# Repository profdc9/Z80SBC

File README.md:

# Z80 Single Board Computer

This is a PCB layout by Daniel Marks of Grant Searle's 9 chip CP/M computer as obtained from

http://searle.x10host.com/cpm/index.html

You need to follow his instructions on how to flash the memory and install CP/M.

http://searle.x10host.com/cpm/z80sbcFiles.zip

This design uses a 28C256 (32k X 8 EEPROM) rather than the original 27128 (16 x 8 EPROM).  JP6 needs to be set to the 16K setting, and only the first 16K of the EEPROM needs to be programmed.

I have added a 8255A peripheral interface and a SPI serial peripheral interface port.  I plan on modifying the SD card driver to use the faster hardware on this board, using the SD card loader here:

http://xepb.org/dtz/sgsbcsd.html

The SPI peripheral will hopefully allow other hardware to be easily added such as an ethernet interface (Wiznet or enc28j60) for TCP/IP, a SPI LCD for display, etc.  JP2 selects the clockspeed of the SPI, either 1/2 of 7.3278 MHz (slow clock) or 16 MHz (fast clock).

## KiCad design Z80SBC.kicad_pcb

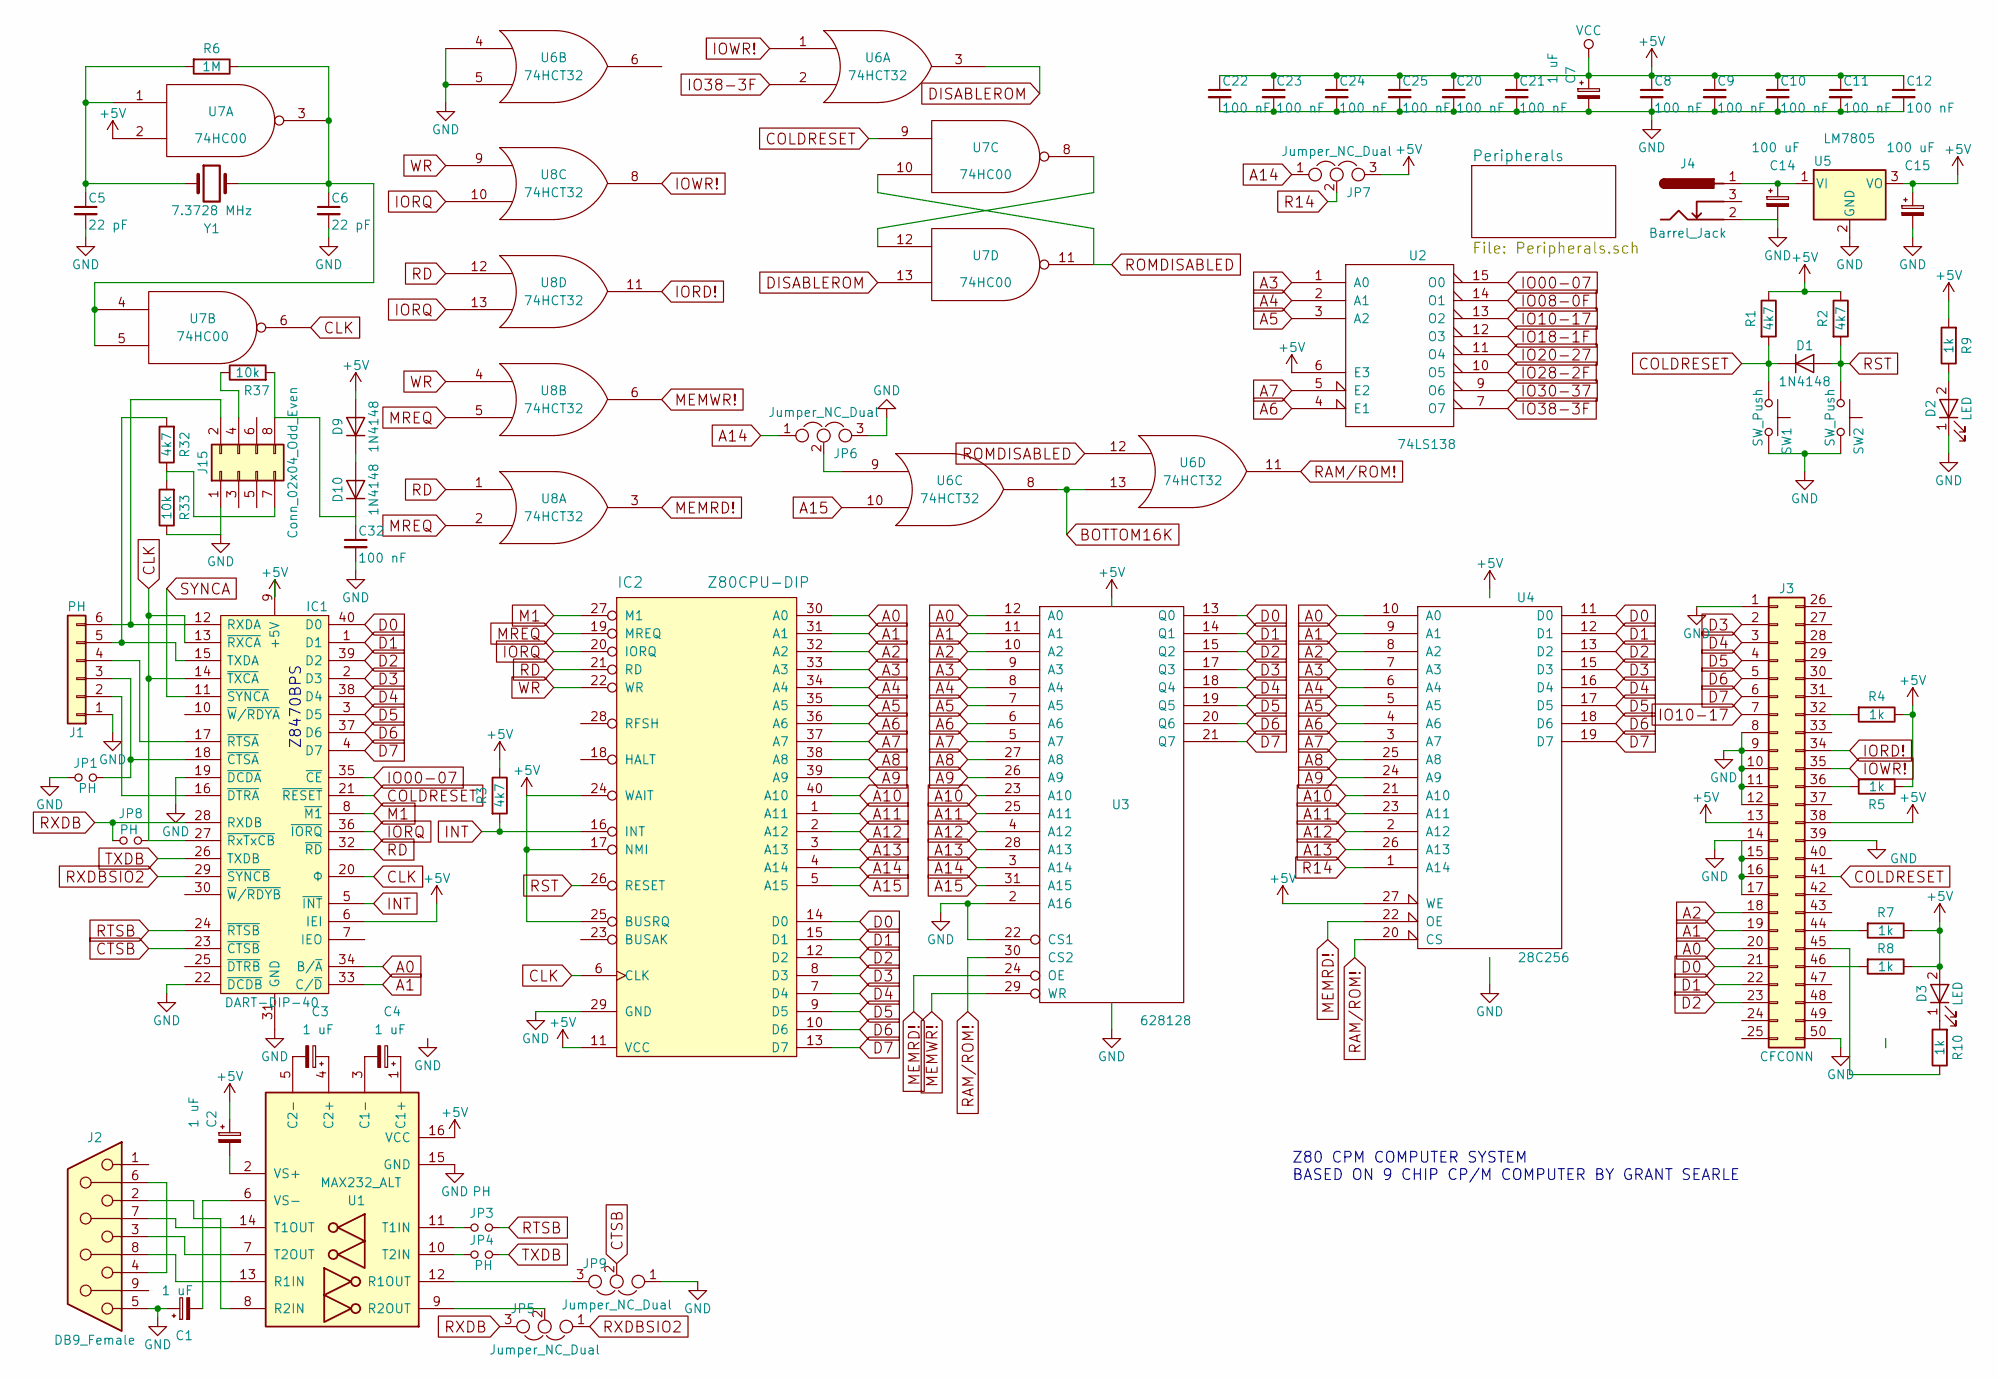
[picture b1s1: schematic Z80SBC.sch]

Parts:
C1, C2, C3, C4, C7: 1 uF; CP_Radial_D5.0mm_P2.50mm
C5, C6: 22 pF; C_Disc_D5.0mm_W2.5mm_P5.00mm
C8, C9, C10, C11, C12, C20, C21, C22, C23, C24, C25, C32: 100 nF; C_Disc_D5.0mm_W2.5mm_P2.50mm
C14, C15: 100 uF; CP_Radial_D5.0mm_P2.50mm
D1, D9, D10: 1N4148; D_DO-35_SOD27_P7.62mm_Horizontal
D2, D3: LED; LED_D3.0mm
IC1: DART-DIP-40; DIP-40_W15.24mm_Socket; Manufacturer_Part_Number Z84C4206PEG; Mouser Part Number 692-Z84C4206PEG
IC2: Z80CPU-DIP; DIP-40_W15.24mm_Socket
J1: PH; Pin_Header_Straight_1x06_Pitch2.54mm
J2: DB9_Female; DSUB-9_Female_Horizontal_P2.77x2.84mm_EdgePinOffset4.94mm_H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
J3: CFCONN; Pin_Header_Straight_2x25_Pitch1.27mm_Rev
J4: Barrel_Jack; BARREL_JACK
J15: Conn_02x04_Odd_Even; Pin_Header_Straight_2x04_Pitch2.54mm_Flipped
JP1, JP3, JP4, JP8: PH; Pin_Header_Straight_1x02_Pitch2.54mm
JP5, JP6, JP7, JP9: Jumper_NC_Dual; Pin_Header_Straight_1x03_Pitch2.54mm
R1, R2, R3, R32: 4k7; R_Axial_DIN0207_L6.3mm_D2.5mm_P7.62mm_Horizontal
R4, R5, R7, R8, R9, R10: 1k; R_Axial_DIN0207_L6.3mm_D2.5mm_P7.62mm_Horizontal
R6: 1M; R_Axial_DIN0207_L6.3mm_D2.5mm_P7.62mm_Horizontal
R33, R37: 10k; R_Axial_DIN0207_L6.3mm_D2.5mm_P7.62mm_Horizontal
SW1, SW2: SW_Push; SW_PUSH_6mm
U1: MAX232_ALT; DIP-16_W7.62mm_Socket
U2: 74LS138; DIP-16_W7.62mm_Socket
U3: 628128; DIP-32_W15.24mm_Socket
U4: 28C256; DIP-28_W15.24mm_Socket
U5: LM7805; TO-220-3_Vertical
U6, U8: 74HCT32; DIP-14_W7.62mm_Socket
U7: 74HC00; DIP-14_W7.62mm_Socket
Y1: 7.3728 MHz; Crystal_HC49-U_Vertical

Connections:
+5V: C2.1, C7.1, C8.1, C9.1, C10.1, C11.1, C12.1, C15.1, C20.1, C21.1, C22.1, C23.1, C24.1, C25.1, D3.2 (A), D9.2 (A), IC1.6 (IEI), IC1.9 (+5V), IC2.11 (VCC), IC2.17 (NMI), IC2.24 (WAIT), IC2.25 (BUSRQ), J3.13, J3.38, JP7.3, R1.1, R2.1, R3.1, R4.1, R5.1, R7.1, R8.1, R9.2, U1.16 (VCC), U2.6 (E3), U2.16 (VCC), U3.32 (VCC), U4.27 (WE), U4.28 (VCC), U5.3 (VO), U6.14 (VCC), U7.2, U7.14 (VCC), U8.14 (VCC); also elsewhere on the board
A0: IC1.34 (B/~A), IC2.30 (A0), J3.20, U3.12 (A0), U4.10 (A0); also elsewhere on the board
A1: IC1.33 (C/~D), IC2.31 (A1), J3.19, U3.11 (A1), U4.9 (A1); also elsewhere on the board
A2: IC2.32 (A2), J3.18, U3.10 (A2), U4.8 (A2)
A3: IC2.33 (A3), U2.1 (A0), U3.9 (A3), U4.7 (A3)
A4: IC2.34 (A4), U2.2 (A1), U3.8 (A4), U4.6 (A4)
A5: IC2.35 (A5), U2.3 (A2), U3.7 (A5), U4.5 (A5)
A6: IC2.36 (A6), U2.4 (E1), U3.6 (A6), U4.4 (A6)
A7: IC2.37 (A7), U2.5 (E2), U3.5 (A7), U4.3 (A7)
A8: IC2.38 (A8), U3.27 (A8), U4.25 (A8)
A9: IC2.39 (A9), U3.26 (A9), U4.24 (A9)
A10: IC2.40 (A10), U3.23 (A10), U4.21 (A10)
A11: IC2.1 (A11), U3.25 (A11), U4.23 (A11)
A12: IC2.2 (A12), U3.4 (A12), U4.2 (A12)
A13: IC2.3 (A13), U3.28 (A13), U4.26 (A13)
A14: IC2.4 (A14), JP6.1, JP7.1, U3.3 (A14)
A15: IC2.5 (A15), U3.31 (A15), U6.10
BOTTOM16K: U6.8, U6.13
CLK: IC1.13 (~RXCA), IC1.14 (~TXCA), IC1.20 (Φ), IC1.27 (~RxTxCB), IC2.6 (CLK), JP8.1, U7.6; also elsewhere on the board
COLDRESET: D1.1 (K), IC1.21 (~RESET), J3.41, R1.2, SW1.1, U7.9; also elsewhere on the board
CTSB: IC1.23 (~CTSB), JP9.2
D0: IC1.40 (D0), IC2.14 (D0), J3.21, U3.13 (Q0), U4.11 (D0); also elsewhere on the board
D1: IC1.1 (D1), IC2.15 (D1), J3.22, U3.14 (Q1), U4.12 (D1); also elsewhere on the board
D2: IC1.39 (D2), IC2.12 (D2), J3.23, U3.15 (Q2), U4.13 (D2); also elsewhere on the board
D3: IC1.2 (D3), IC2.8 (D3), J3.2, U3.17 (Q3), U4.15 (D3); also elsewhere on the board
D4: IC1.38 (D4), IC2.7 (D4), J3.3, U3.18 (Q4), U4.16 (D4); also elsewhere on the board
D5: IC1.3 (D5), IC2.9 (D5), J3.4, U3.19 (Q5), U4.17 (D5); also elsewhere on the board
D6: IC1.37 (D6), IC2.10 (D6), J3.5, U3.20 (Q6), U4.18 (D6); also elsewhere on the board
D7: IC1.4 (D7), IC2.13 (D7), J3.6, U3.21 (Q7), U4.19 (D7); also elsewhere on the board
DISABLEROM: U6.3, U7.13
GND: C1.1, C5.2, C6.2, C7.2, C8.2, C9.2, C10.2, C11.2, C12.2, C14.2, C15.2, C20.2, C21.2, C22.2, C23.2, C24.2, C25.2, C32.2, D2.1 (K), IC1.19 (~DCDA), IC1.22 (~DCDB), IC1.31 (GND), IC2.29 (GND), J1.1, J2.5, J3.1, J3.8, J3.9, J3.10, J3.11, J3.12, J3.14, J3.15, J3.16, J3.17, J3.39, J3.50, J4.2, J15.1, JP1.1, JP6.3, JP9.1, R33.1, SW1.2, SW2.2, U1.15 (GND), U2.8 (GND), U3.2 (A16), U3.16 (GND), U3.22 (CS1), U4.14 (GND), U5.2 (GND), U6.4, U6.5, U6.7 (GND), U7.7 (GND), U8.7 (GND); also elsewhere on the board
INT: IC1.5 (~INT), IC2.16 (INT), R3.2
IO00-07: IC1.35 (~CE), U2.15 (O0)
IO08-0F: U2.14 (O1)
IO10-17: J3.7, U2.13 (O2)
IO18-1F: U2.12 (O3); also elsewhere on the board
IO20-27: U2.11 (O4); also elsewhere on the board
IO28-2F: U2.10 (O5)
IO30-37: U2.9 (O6)
IO38-3F: U2.7 (O7), U6.2
IORD!: J3.34, U8.11; also elsewhere on the board
IORQ: IC1.36 (~IORQ), IC2.20 (IORQ), U8.10, U8.13
IOWR!: J3.35, U6.1, U8.8; also elsewhere on the board
M1: IC1.8 (~M1), IC2.27 (M1)
MEMRD!: U3.24 (OE), U4.22 (OE), U8.3
MEMWR!: U3.29 (WR), U8.6
MREQ: IC2.19 (MREQ), U8.2, U8.5
unnamed: C1.2, U1.6 (VS-)
unnamed: C2.2, U1.2 (VS+)
unnamed: C3.1, U1.4 (C2+)
unnamed: C3.2, U1.5 (C2-)
unnamed: C4.1, U1.1 (C1+)
unnamed: C4.2, U1.3 (C1-)
unnamed: C5.1, R6.2, U7.1, Y1.1
unnamed: C6.1, R6.1, U7.3, U7.4, U7.5, Y1.2
unnamed: C14.1, J4.1, U5.1 (VI)
unnamed: C32.1, D10.1 (K), J15.8, R37.2
unnamed: D2.2 (A), R9.1
unnamed: D3.1 (K), R10.2
unnamed: D9.1 (K), D10.2 (A)
unnamed: IC1.12 (RXDA), J1.6, J15.2
unnamed: IC1.15 (TXDA), J1.5, R32.2
unnamed: IC1.16 (~DTRA), J1.2
unnamed: IC1.17 (~RTSA), J1.4
unnamed: IC1.18 (~CTSA), J1.3, JP1.2
unnamed: J2.2, U1.8 (R2IN)
unnamed: J2.3, U1.7 (T2OUT)
unnamed: J2.4, J2.6
unnamed: J2.7, U1.14 (T1OUT)
unnamed: J2.8, U1.13 (R1IN)
unnamed: J3.32, R4.2
unnamed: J3.36, R5.2
unnamed: J3.44, R7.2
unnamed: J3.45, R10.1
unnamed: J3.46, R8.2
unnamed: J15.4, R37.1
unnamed: J15.7, R32.1, R33.2
unnamed: JP3.1, U1.11 (T1IN)
unnamed: JP4.1, U1.10 (T2IN)
unnamed: JP5.2, U1.9 (R2OUT)
unnamed: JP6.2, U6.9
unnamed: JP9.3, U1.12 (R1OUT)
unnamed: U7.8, U7.12
R14: JP7.2, U4.1 (A14)
RAM/ROM!: U3.30 (CS2), U4.20 (CS), U6.11
RD: IC1.32 (~RD), IC2.21 (RD), U8.1, U8.12
ROMDISABLED: U6.12, U7.10, U7.11
RST: D1.2 (A), IC2.26 (RESET), R2.2, SW2.1
RTSB: IC1.24 (~RTSB), JP3.2
RXDB: IC1.28 (RXDB), JP5.3, JP8.2
RXDBSIO2: IC1.29 (~SYNCB), JP5.1
SYNCA: IC1.11 (~SYNCA); also elsewhere on the board
TXDB: IC1.26 (TXDB), JP4.2
WR: IC2.22 (WR), U8.4, U8.9

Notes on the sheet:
Z80 CPM COMPUTER SYSTEM BASED ON 9 CHIP CP/M COMPUTER BY GRANT SEARLE
Z8470BPS

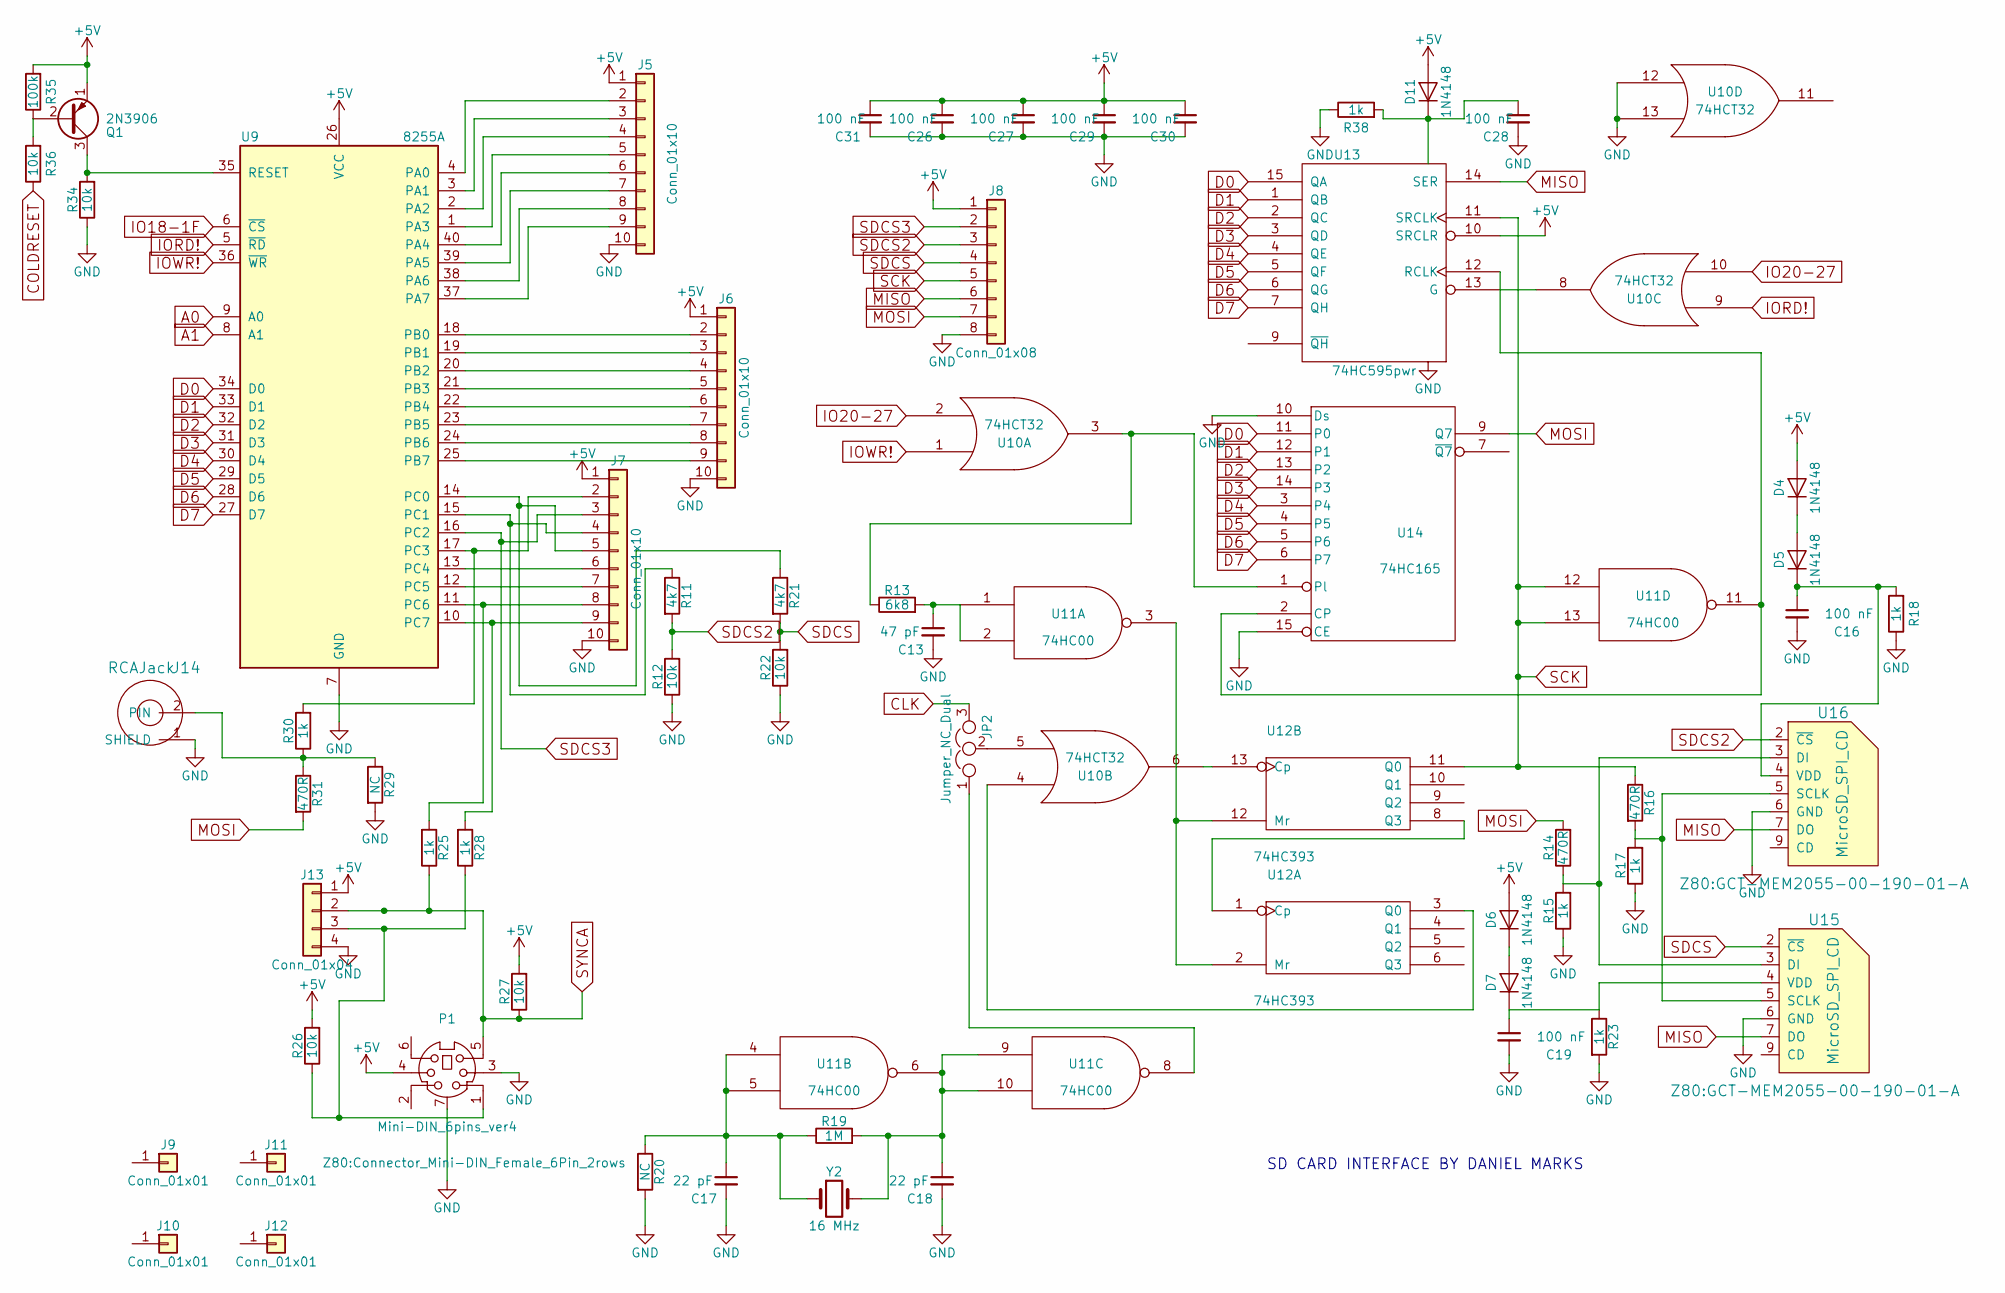
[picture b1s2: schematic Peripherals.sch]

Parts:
C13: 47 pF; C_Disc_D5.0mm_W2.5mm_P5.00mm
C16, C19: 100 nF; C_Disc_D5.0mm_W2.5mm_P5.00mm
C17, C18: 22 pF; C_Disc_D5.0mm_W2.5mm_P5.00mm
C26, C27, C28, C29, C30, C31: 100 nF; C_Disc_D5.0mm_W2.5mm_P2.50mm
D4, D5, D6, D7, D11: 1N4148; D_DO-35_SOD27_P7.62mm_Horizontal
J5, J6, J7: Conn_01x10; Pin_Header_Straight_1x10_Pitch2.54mm
J8: Conn_01x08; Pin_Header_Straight_1x08_Pitch2.54mm
J9, J10, J11, J12: Conn_01x01; MountingHole_3.2mm_M3
J13: Conn_01x04; Pin_Header_Straight_1x04_Pitch2.54mm
J14: RCAJack; RCAConnectorCommon
JP2: Jumper_NC_Dual; Pin_Header_Straight_1x03_Pitch2.54mm
P1: Mini-DIN_6pins_ver4; Connector_Mini-DIN_Female_6Pin_2rows
Q1: 2N3906; TO-92_Inline_Wide
R11, R21: 4k7; R_Axial_DIN0207_L6.3mm_D2.5mm_P7.62mm_Horizontal
R12, R22, R26, R27, R34, R36: 10k; R_Axial_DIN0207_L6.3mm_D2.5mm_P7.62mm_Horizontal
R13: 6k8; R_Axial_DIN0207_L6.3mm_D2.5mm_P7.62mm_Horizontal
R14, R16, R31: 470R; R_Axial_DIN0207_L6.3mm_D2.5mm_P7.62mm_Horizontal
R15, R17, R18, R23, R25, R28, R30, R38: 1k; R_Axial_DIN0207_L6.3mm_D2.5mm_P7.62mm_Horizontal
R19: 1M; R_Axial_DIN0207_L6.3mm_D2.5mm_P7.62mm_Horizontal
R20, R29: NC; R_Axial_DIN0207_L6.3mm_D2.5mm_P7.62mm_Horizontal
R35: 100k; R_Axial_DIN0207_L6.3mm_D2.5mm_P7.62mm_Horizontal
U9: 8255A; DIP-40_W15.24mm_Socket
U10: 74HCT32; DIP-14_W7.62mm_Socket
U11: 74HC00; DIP-14_W7.62mm_Socket
U12: 74HC393; DIP-14_W7.62mm_Socket
U13: 74HC595pwr
U14: 74HC165; DIP-16_W7.62mm_Socket
U15, U16: MicroSD_SPI_CD; GCT-MEM2055-00-190-01-A
Y2: 16 MHz; Crystal_HC49-U_Vertical

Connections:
+5V: C26.1, C27.1, C29.1, C30.1, C31.1, D4.2 (A), D6.2 (A), D11.2 (A), J5.1, J6.1, J7.1, J8.1, J13.1, P1.4, Q1.1 (E), R26.2, R27.2, R35.2, U9.26 (VCC), U10.14 (VCC), U11.14 (VCC), U12.14 (VCC), U13.10 (SRCLR), U14.16 (VCC); also elsewhere on the board
A0: U9.9 (A0); also elsewhere on the board
A1: U9.8 (A1); also elsewhere on the board
CLK: JP2.3; also elsewhere on the board
COLDRESET: R36.1; also elsewhere on the board
D0: U9.34 (D0), U13.15 (QA), U14.11 (P0); also elsewhere on the board
D1: U9.33 (D1), U13.1 (QB), U14.12 (P1); also elsewhere on the board
D2: U9.32 (D2), U13.2 (QC), U14.13 (P2); also elsewhere on the board
D3: U9.31 (D3), U13.3 (QD), U14.14 (P3); also elsewhere on the board
D4: U9.30 (D4), U13.4 (QE), U14.3 (P4); also elsewhere on the board
D5: U9.29 (D5), U13.5 (QF), U14.4 (P5); also elsewhere on the board
D6: U9.28 (D6), U13.6 (QG), U14.5 (P6); also elsewhere on the board
D7: U9.27 (D7), U13.7 (QH), U14.6 (P7); also elsewhere on the board
GND: C13.2, C16.2, C17.2, C18.2, C19.2, C26.2, C27.2, C28.2, C29.2, C30.2, C31.2, J5.10, J6.10, J7.10, J8.8, J13.4, J14.1 (SHIELD), P1.3, P1.7 (Shell), R12.1, R15.1, R17.1, R18.1, R20.2, R22.1, R23.2, R29.2, R34.1, R38.1, U9.7 (GND), U10.7 (GND), U10.12, U10.13, U11.7 (GND), U12.7 (GND), U13.8 (GND), U14.8 (GND), U14.10 (Ds), U14.15 (CE), U15.6 (GND), U16.6 (GND); also elsewhere on the board
IO18-1F: U9.6 (~CS~); also elsewhere on the board
IO20-27: U10.2, U10.10; also elsewhere on the board
IORD!: U9.5 (~RD~), U10.9; also elsewhere on the board
IOWR!: U9.36 (~WR~), U10.1; also elsewhere on the board
MISO: J8.6, U13.14 (SER), U15.7 (DO), U16.7 (DO)
MOSI: J8.7, R14.2, R31.2, U14.9 (Q7)
unnamed: C13.1, R13.2, U11.1, U11.2
unnamed: C16.1, D5.1 (K), R18.2, U16.4 (VDD)
unnamed: C17.1, R19.1, R20.1, U11.4, U11.5, Y2.1
unnamed: C18.1, R19.2, U11.6, U11.9, U11.10, Y2.2
unnamed: C19.1, D7.1 (K), R23.1, U15.4 (VDD)
unnamed: C28.1, D11.1 (K), R38.2, U13.16 (VCC)
unnamed: D4.1 (K), D5.2 (A)
unnamed: D6.1 (K), D7.2 (A)
unnamed: J5.2, U9.4 (PA0)
unnamed: J5.3, U9.3 (PA1)
unnamed: J5.4, U9.2 (PA2)
unnamed: J5.5, U9.1 (PA3)
unnamed: J5.6, U9.40 (PA4)
unnamed: J5.7, U9.39 (PA5)
unnamed: J5.8, U9.38 (PA6)
unnamed: J5.9, U9.37 (PA7)
unnamed: J6.2, U9.18 (PB0)
unnamed: J6.3, U9.19 (PB1)
unnamed: J6.4, U9.20 (PB2)
unnamed: J6.5, U9.21 (PB3)
unnamed: J6.6, U9.22 (PB4)
unnamed: J6.7, U9.23 (PB5)
unnamed: J6.8, U9.24 (PB6)
unnamed: J6.9, U9.25 (PB7)
unnamed: J7.2, R30.2, U9.17 (PC3)
unnamed: J7.4, R11.1, U9.15 (PC1)
unnamed: J7.5, R21.1, U9.14 (PC0)
unnamed: J7.6, U9.13 (PC4)
unnamed: J7.7, U9.12 (PC5)
unnamed: J7.8, R25.2, U9.11 (PC6)
unnamed: J7.9, R28.2, U9.10 (PC7)
unnamed: J13.3, P1.1, R26.1, R28.1
unnamed: J14.2 (PIN), R29.1, R30.1, R31.1
unnamed: JP2.1, U11.8
unnamed: JP2.2, U10.5
unnamed: Q1.2 (B), R35.1, R36.2
unnamed: Q1.3 (C), R34.2, U9.35 (RESET)
unnamed: R13.1, U10.3, U14.1 (Pl)
unnamed: R14.1, R15.2, U15.3 (DI), U16.3 (DI)
unnamed: R16.2, R17.2, U15.5 (SCLK), U16.5 (SCLK)
unnamed: U10.4, U12.3 (Q0)
unnamed: U10.6, U12.13 (Cp)
unnamed: U10.8, U13.13 (G)
unnamed: U11.3, U12.2 (Mr), U12.12 (Mr)
unnamed: U11.11, U13.12 (RCLK), U14.2 (CP)
unnamed: U12.1 (Cp), U12.8 (Q3)
SCK: J8.5, R16.1, U11.12, U11.13, U12.11 (Q0), U13.11 (SRCLK)
SDCS: J8.4, R21.2, R22.2, U15.2 (~CS)
SDCS2: J8.3, R11.2, R12.2, U16.2 (~CS)
SDCS3: J7.3, J8.2, U9.16 (PC2)
SYNCA: J13.2, P1.5, R25.1, R27.1; also elsewhere on the board

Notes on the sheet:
SD CARD INTERFACE BY DANIEL MARKS

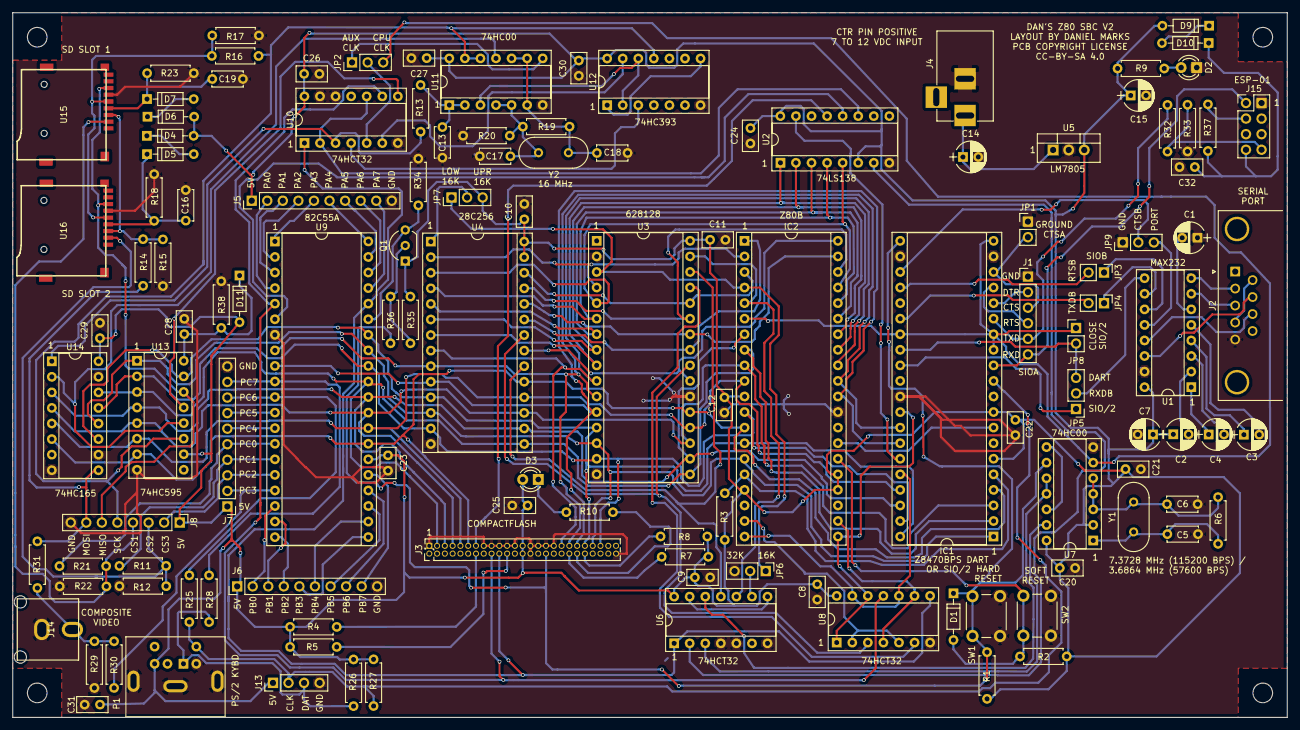
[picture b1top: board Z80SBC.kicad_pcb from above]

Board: 2 copper layers, 208.0 x 115.0 mm, 127 parts (0 on the bottom side), 143 nets.

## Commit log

2021-04-15 With dual clock output
2021-04-19 Added README.md
2021-04-19 revised README.md
2021-04-20 Added PS/2 keyboard input
2021-04-29 Added ESP-01 and video output
2021-08-01 Fixed jumpers, CF card position, ESP-01 enable
2021-08-01 Schematic is back
2021-08-09 Added SD card driver
2021-08-09 ROM CPM archive added
2021-08-09 Added ROMCPM archive
2021-08-14 Fixed PS/2 interrupt line
2021-08-17 Fixed SDHC support, added extra configuration jumpers
2021-08-18 Modified video output
2021-08-22 Moved around port B/C pins to separate input and output groups
2021-08-22 Checking for update

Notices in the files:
Z80SBC.kicad_pcb:
PCB COPYRIGHT LICENSE
CC-BY-SA 4.0
